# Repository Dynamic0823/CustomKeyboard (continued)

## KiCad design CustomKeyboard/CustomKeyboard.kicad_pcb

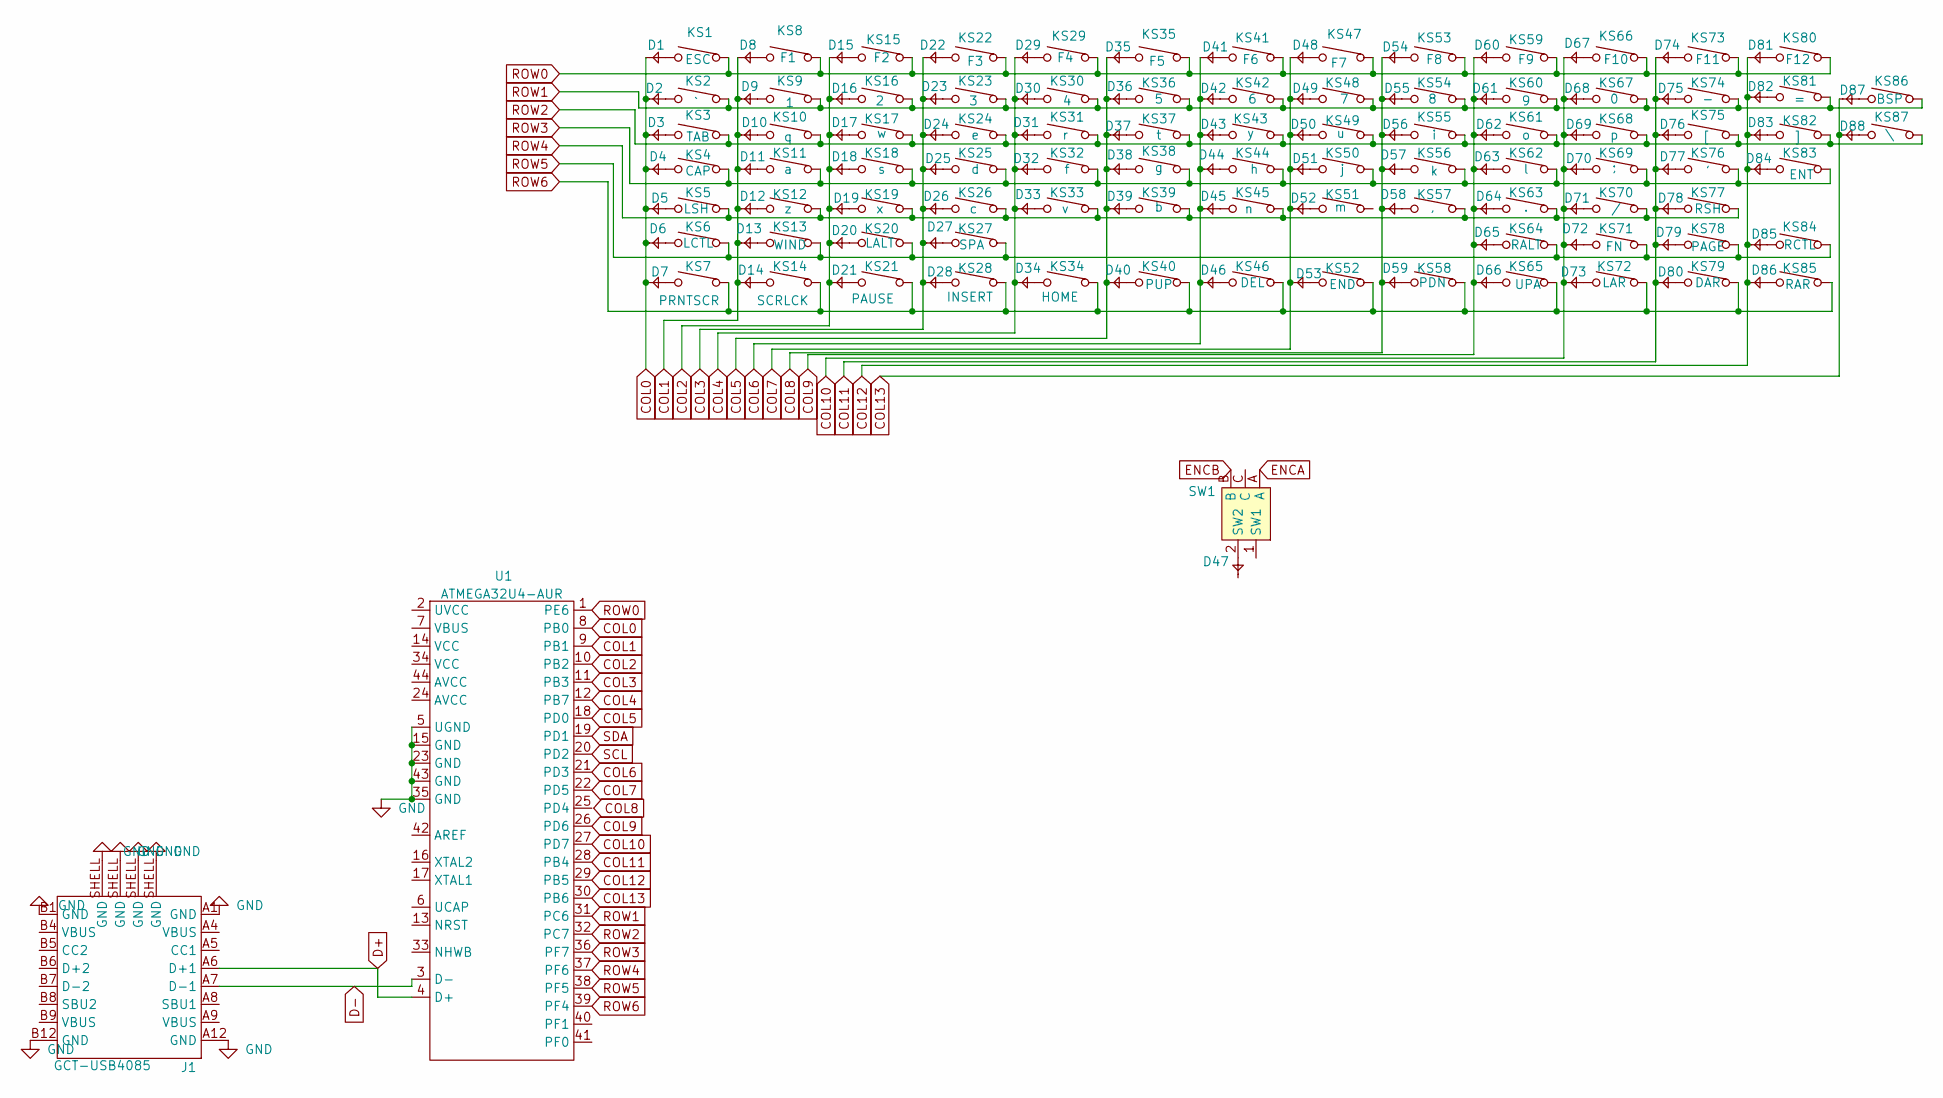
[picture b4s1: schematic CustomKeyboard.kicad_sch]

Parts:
D1, D2, D3, D4, D5, D6, D7, D8, D9, D10, D11, D12, D13, D14, D15, D16, D17, D18, D19, D20, D21, D22, D23, D24, D25, D26, D27, D28, D29, D30, D31, D32, D33, D34, D35, D36, D37, D38, D39, D40, D41, D42, D43, D44, D45, D46, D47, D48, D49, D50, D51, D52, D53, D54, D55, D56, D57, D58, D59, D60, D61, D62, D63, D64, D65, D66, D67, D68, D69, D70, D71, D72, D73, D74, D75, D76, D77, D78, D79, D80, D81, D82, D83, D84, D85, D86, D87, D88: 1N4148WX-TP; SOD323
J1: GCT-USB4085; USB4085-GF-A; DigikeyPN 2073-USB4085-GF-ATR-ND
KS1: ESC; CherryMx
KS2: `; CherryMx
KS3: TAB; CherryMx
KS4: CAP; CherryMx
KS5: LSH; CherryMx
KS6: LCTL; CherryMx
KS7: PRNTSCR; CherryMx
KS8: F1; CherryMx
KS9: 1; CherryMx
KS10: q; CherryMx
KS11: a; CherryMx
KS12: z; CherryMx
KS13: WIND; CherryMx
KS14: SCRLCK; CherryMx
KS15: F2; CherryMx
KS16: 2; CherryMx
KS17: w; CherryMx
KS18: s; CherryMx
KS19: x; CherryMx
KS20: LALT; CherryMx
KS21: PAUSE; CherryMx
KS22: F3; CherryMx
KS23: 3; CherryMx
KS24: e; CherryMx
KS25: d; CherryMx
KS26: c; CherryMx
KS27: SPA; CherryMx
KS28: INSERT; CherryMx
KS29: F4; CherryMx
KS30: 4; CherryMx
KS31: r; CherryMx
KS32: f; CherryMx
KS33: v; CherryMx
KS34: HOME; CherryMx
KS35: F5; CherryMx
KS36: 5; CherryMx
KS37: t; CherryMx
KS38: g; CherryMx
KS39: b; CherryMx
KS40: PUP; CherryMx
KS41: F6; CherryMx
KS42: 6; CherryMx
KS43: y; CherryMx
KS44: h; CherryMx
KS45: n; CherryMx
KS46: DEL; CherryMx
KS47: F7; CherryMx
KS48: 7; CherryMx
KS49: u; CherryMx
KS50: j; CherryMx
KS51: m; CherryMx
KS52: END; CherryMx
KS53: F8; CherryMx
KS54: 8; CherryMx
KS55: i; CherryMx
KS56: k; CherryMx
KS57: ,; CherryMx
KS58: PDN; CherryMx
KS59: F9; CherryMx
KS60: 9; CherryMx
KS61: o; CherryMx
KS62: l; CherryMx
KS63: .; CherryMx
KS64: RALT; CherryMx
KS65: UPA; CherryMx
KS66: F10; CherryMx
KS67: 0; CherryMx
KS68: p; CherryMx
KS69: ;; CherryMx
KS70: /; CherryMx
KS71: FN; CherryMx
KS72: LAR; CherryMx
KS73: F11; CherryMx
KS74: -; CherryMx
KS75: [; CherryMx
KS76: '; CherryMx
KS77: RSH; CherryMx
KS78: PAGE; CherryMx
KS79: DAR; CherryMx
KS80: F12; CherryMx
KS81: =; CherryMx
KS82: ]; CherryMx
KS83: ENT; CherryMx
KS84: RCTL; CherryMx
KS85: RAR; CherryMx
KS86: BSP; CherryMx
KS87: \; CherryMx
SW1: PEC11H-RotaryEncoderSwitch
U1: ATMEGA32U4-AUR

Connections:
COL0: D1.2, D2.2, D3.2, D4.2, D5.2, D6.2, D7.2, U1.8 (PB0)
COL1: D8.2, D9.2, D10.2, D11.2, D12.2, D13.2, D14.2, U1.9 (PB1)
COL2: D15.2, D16.2, D17.2, D18.2, D19.2, D20.2, D21.2, U1.10 (PB2)
COL3: D22.2, D23.2, D24.2, D25.2, D26.2, D27.2, D28.2, U1.11 (PB3)
COL4: D29.2, D30.2, D31.2, D32.2, D33.2, D34.2, U1.12 (PB7)
COL5: D35.2, D36.2, D37.2, D38.2, D39.2, D40.2, U1.18 (PD0)
COL6: D41.2, D42.2, D43.2, D44.2, D45.2, D46.2, U1.21 (PD3)
COL7: D48.2, D49.2, D50.2, D51.2, D52.2, D53.2, U1.22 (PD5)
COL8: D54.2, D55.2, D56.2, D57.2, D58.2, D59.2
COL9: D60.2, D61.2, D62.2, D63.2, D64.2, D65.2, D66.2, U1.26 (PD6)
COL10: D67.2, D68.2, D69.2, D70.2, D71.2, D72.2, D73.2, U1.27 (PD7)
COL11: D74.2, D75.2, D76.2, D77.2, D78.2, D79.2, D80.2, U1.28 (PB4)
COL13: D87.2, D88.2, SW1.1 (SW1), U1.30 (PB6)
D+: J1.A6 (D+1), U1.4 (D+)
D-: J1.A7 (D-1), U1.3 (D-)
ENCA: SW1.A; also elsewhere on the board
ENCB: SW1.B; also elsewhere on the board
GND: J1.A1 (GND), J1.A12 (GND), J1.B1 (GND), J1.B12 (GND), J1.SHELL (GND), U1.5 (UGND), U1.15 (GND), U1.23 (GND), U1.35 (GND), U1.43 (GND)
unnamed: D1.1, KS1.2
unnamed: D2.1, KS2.2
unnamed: D3.1, KS3.2
unnamed: D4.1, KS4.2
unnamed: D5.1, KS5.2
unnamed: D6.1, KS6.2
unnamed: D7.1, KS7.2
unnamed: D8.1, KS8.2
unnamed: D9.1, KS9.2
unnamed: D10.1, KS10.2
unnamed: D11.1, KS11.2
unnamed: D12.1, KS12.2
unnamed: D13.1, KS13.2
unnamed: D14.1, KS14.2
unnamed: D15.1, KS15.2
unnamed: D16.1, KS16.2
unnamed: D17.1, KS17.2
unnamed: D18.1, KS18.2
unnamed: D19.1, KS19.2
unnamed: D20.1, KS20.2
unnamed: D21.1, KS21.2
unnamed: D22.1, KS22.2
unnamed: D23.1, KS23.2
unnamed: D24.1, KS24.2
unnamed: D25.1, KS25.2
unnamed: D26.1, KS26.2
unnamed: D27.1, KS27.2
unnamed: D28.1, KS28.2
unnamed: D29.1, KS29.2
unnamed: D30.1, KS30.2
unnamed: D31.1, KS31.2
unnamed: D32.1, KS32.2
unnamed: D33.1, KS33.2
unnamed: D34.1, KS34.2
unnamed: D35.1, KS35.2
unnamed: D36.1, KS36.2
unnamed: D37.1, KS37.2
unnamed: D38.1, KS38.2
unnamed: D39.1, KS39.2
unnamed: D40.1, KS40.2
unnamed: D41.1, KS41.2
unnamed: D42.1, KS42.2
unnamed: D43.1, KS43.2
unnamed: D44.1, KS44.2
unnamed: D45.1, KS45.2
unnamed: D46.1, KS46.2
unnamed: D48.1, KS47.2
unnamed: D49.1, KS48.2
unnamed: D50.1, KS49.2
unnamed: D51.1, KS50.2
unnamed: D52.1, KS51.2
unnamed: D53.1, KS52.2
unnamed: D54.1, KS53.2
unnamed: D55.1, KS54.2
unnamed: D56.1, KS55.2
unnamed: D57.1, KS56.2
unnamed: D58.1, KS57.2
unnamed: D59.1, KS58.2
unnamed: D60.1, KS59.2
unnamed: D61.1, KS60.2
unnamed: D62.1, KS61.2
unnamed: D63.1, KS62.2
unnamed: D64.1, KS63.2
unnamed: D65.1, KS64.2
unnamed: D66.1, KS65.2
unnamed: D67.1, KS66.2
unnamed: D68.1, KS67.2
unnamed: D69.1, KS68.2
unnamed: D70.1, KS69.2
unnamed: D71.1, KS70.2
unnamed: D72.1, KS71.2
unnamed: D73.1, KS72.2
unnamed: D74.1, KS73.2
unnamed: D75.1, KS74.2
unnamed: D76.1, KS75.2
unnamed: D77.1, KS76.2
unnamed: D78.1, KS77.2
unnamed: D79.1, KS78.2
unnamed: D80.1, KS79.2
unnamed: D81.1, KS80.2
unnamed: D82.1, KS81.2
unnamed: D83.1, KS82.2
unnamed: D84.1, KS83.2
unnamed: D85.1, KS84.2
unnamed 102: D86.1, KS85.2; also elsewhere on the board
unnamed: D88.1, KS87.2
ROW1: KS2.1, KS9.1, KS16.1, KS23.1, KS30.1, KS36.1, KS42.1, KS48.1, KS54.1, KS60.1, KS67.1, KS74.1, KS81.1, KS86.1, U1.31 (PC6)
ROW2: KS3.1, KS10.1, KS17.1, KS24.1, KS31.1, KS37.1, KS43.1, KS49.1, KS55.1, KS61.1, KS68.1, KS75.1, KS82.1, KS87.1, U1.32 (PC7)
ROW3: KS4.1, KS11.1, KS18.1, KS25.1, KS32.1, KS38.1, KS44.1, KS50.1, KS56.1, KS62.1, KS69.1, KS76.1, KS83.1, U1.36 (PF7)
ROW4: KS5.1, KS12.1, KS19.1, KS26.1, KS33.1, KS39.1, KS45.1, KS57.1, KS63.1, KS70.1, KS77.1, U1.37 (PF6)
ROW5: KS6.1, KS13.1, KS20.1, KS27.1, KS64.1, KS71.1, KS78.1, KS84.1, U1.38 (PF5)
ROW6: KS7.1, KS14.1, KS21.1, KS28.1, KS34.1, KS40.1, KS46.1, KS52.1, KS58.1, KS65.1, KS72.1, KS79.1, KS85.1, U1.39 (PF4)
SCL: U1.20 (PD2)
SDA: U1.19 (PD1)

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
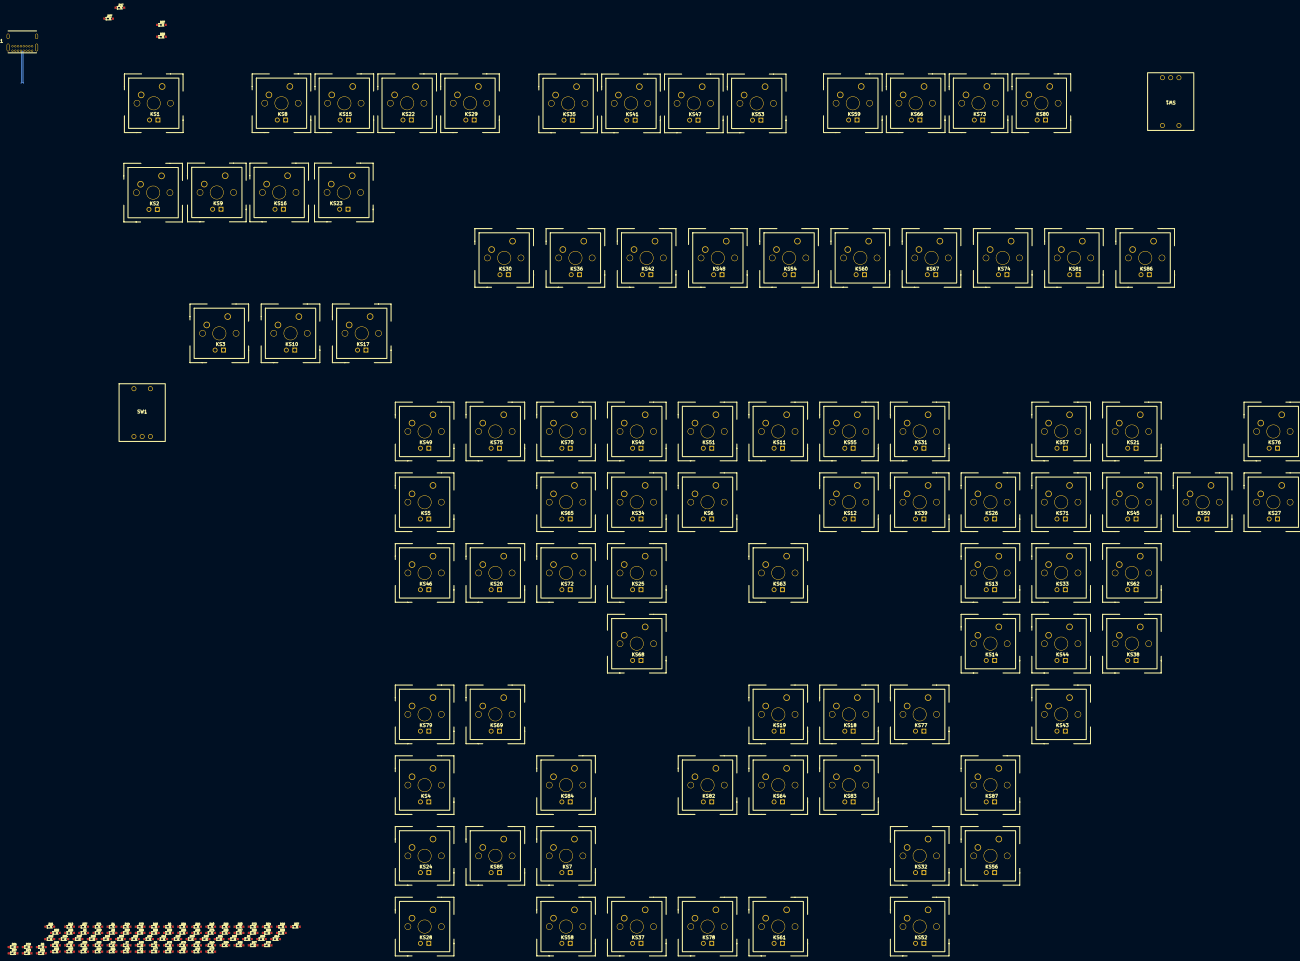
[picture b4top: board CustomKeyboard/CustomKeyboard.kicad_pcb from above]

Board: 2 copper layers, 181 parts (1 on the bottom side), 114 nets.

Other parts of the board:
D86#2, D87#2: 1N4148WX-TP; SOD323
SW1#2: PEC11H-RotaryEncoderSwitch

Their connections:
ENCA: SW1#2.A; also elsewhere on the board
ENCB: SW1#2.B; also elsewhere on the board
unnamed 102: D86#2.1; also elsewhere on the board

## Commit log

2023-12-18 Started Libraries for Symbols and FPS
2023-12-18 Almost done with usb-c footprint(full 24 Pin)
2023-12-18 Added gitignore with *~ for space saving
2023-12-18 Small Updates before wiping laptop
2023-12-19 Finished Footprints and added Backups to gitignore, Started Schematic and layout for keys
2023-12-19 Removed Backups from folder and fixed gitignore for backus
2023-12-25 Finished Initial Footprints and started layout
2023-12-28 stuff
2025-09-28 Starting A fresh branch, with the intention of splitting the keyboard into separtate PCBs for the keyboard and the mcu/compute
2025-09-28 Added Empty Kicad Projects for the 3 main designs
2025-09-29 Schematic and Initial layout for Keyboard PCB
2025-10-01 Finished First Pass of Schematic and Layout
2025-10-03 First rev of keyboard main board complete, starting on controller board next
2025-10-03 Started Schematic for Controller PCB
2025-10-11 Started Controller Routing
2025-10-25 Removed Some Temporary Files
2025-10-25 Reworking the layout, and changed the ESD Protection
2025-10-26 Finished First Rev Of Both PCB's, after testing fits in freecad, will move onto ordrering board
2025-10-26 Last Commit Before JLC Order, Looking to do BOM next
2025-10-27 Added an extra mounting hole to controller board -I Noticed some import errors on the usb-c fp when I cloned this on my laptop, go back and review all pads before sending to JLC
2025-10-27 USB connector was giving some net problems, swapped with a different one
2025-12-02 Push Before PC Upgrad
2026-04-18 Reworking Keyboard PCB, Agian
2026-04-25 Complete rework with hot swap sockets and high density pin board to board connectors
